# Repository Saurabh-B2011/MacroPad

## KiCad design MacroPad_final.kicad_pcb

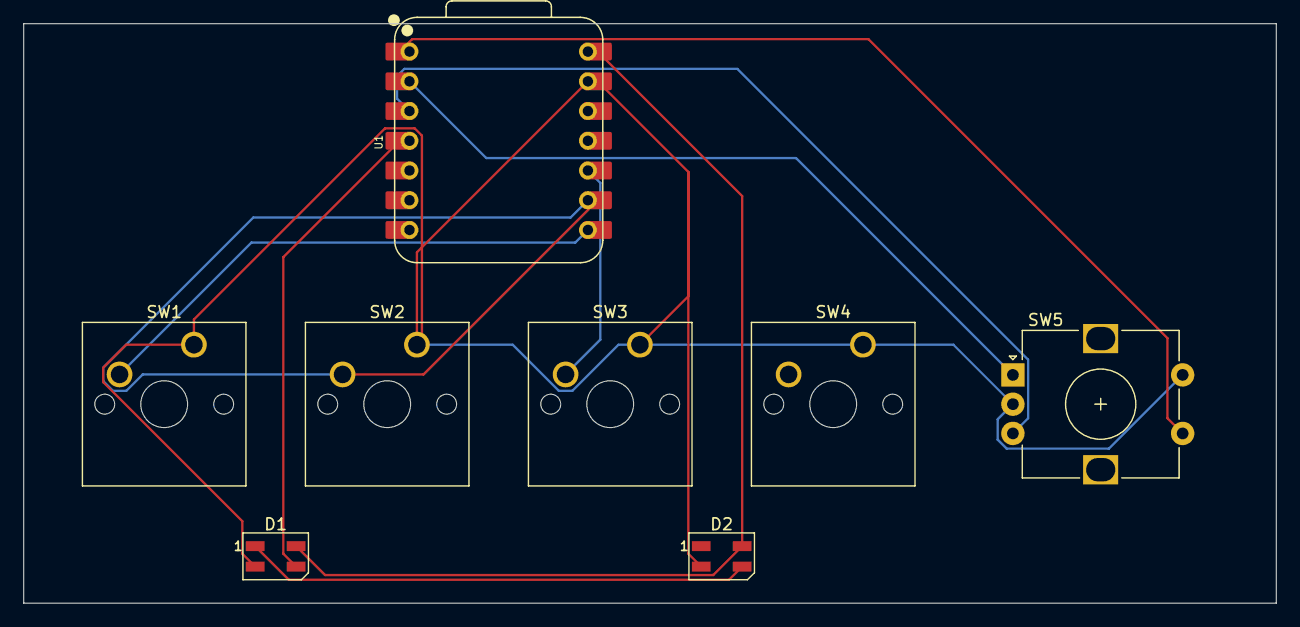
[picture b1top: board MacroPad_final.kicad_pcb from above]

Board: 2 copper layers, 107.0 x 49.5 mm, 8 parts (0 on the bottom side), 10 nets.

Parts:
D1, D2: SK6812MINI; LED_SK6812MINI_PLCC4_3.5x3.5mm_P1.75mm
SW1, SW2, SW3, SW4: SW_Push; SW_Cherry_MX_1.00u_PCB
SW5: RotaryEncoder_Switch; RotaryEncoder_Alps_EC12E-Switch_Vertical_H20mm
U1: XIAO-RP2040-SMD; XIAO-RP2040-DIP

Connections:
+5V: D1.4 (VDD), D2.4 (VDD), U1.14 (VBUS)
GND: D1.2 (VSS), D2.2 (VSS), SW1.1, SW2.1, SW3.1, SW4.1 (1_1), SW5.C, SW5.S1, U1.13 (GND)
unnamed: D1.3 (DIN), U1.4 (D3)
unnamed: D1.1 (DOUT), D2.3 (DIN)
unnamed: SW5.S2, U1.1 (D0)
unnamed: SW5.A, U1.2 (D1)
unnamed: SW5.B, U1.3 (D2)
unnamed: SW1.2, U1.8 (D7)
unnamed: SW2.2, U1.9 (D8)
unnamed: SW3.2, U1.10 (D9)
